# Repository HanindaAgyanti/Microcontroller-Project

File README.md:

<h1 align="left">
  Audio Sistem Pengingat Penyiraman Tanaman
<br></br>

</h1>

## Daftar Isi
* <a href="#deskripsi">Deskripsi</a>
* <a href="#komponen">Komponen</a>
* <a href="#electric">Electric</a>
  - <a href="#blok-diagram">Blok Diagram</a>
  - <a href="#simulasi-tinkercad">Simulasi Tinkercad</a>
  - <a href="#schematic">Schematic</a>
  - <a href="#pcb">PCB</a>
  - <a href="#audio">Audio</a>
* <a href="#3d-design">3D Design</a>
  - <a href="#preview-img">Preview Img</a>
  - <a href="#preview-video">Preview Video</a>
* <a href="#program">Program</a>
  - <a href="#flowchart">Flowchart</a>
  - <a href="arduino-program">Arduino Program</a>
* <a href="#progress">Progress</a>
* <a href="#iklan-produk">Iklan Produk</a>
* <a href="#contact-person">Contact Person</a>
<br></br>

## Deskripsi
<div align="justify">
Sebuah projek mata kuliah Workshop Mikrokontroler membuat Sistem Pendeteksi Penyiram Tanaman diharap mampu membantu masyarakat diberbagai kalangan usia untuk dapat menentukan waktu yang tepat dalam menyiram tanaman menggunakan sensor kelembapan. Dengan adanya project ini juga dapat mencapai sektor lingkungan khususnya pada taman, agar tanaman dapat lebih segar dan tidak layu. Project ini juga sangat bermanfaat untuk sektor pertanian, perkebunan, serta perladangan.<br></br>
  
`#Audio Sistem Pengingat Penyiraman Tanaman` `#Workshop Mikrokontroler` `#Teknik Elektronika` `#Politeknik Elektronika Negeri Surabaya`
</div><br></br>

## Anggota Kelompok
### Rayzanta Ilham D (2122500033)<br> Jobdesk: 3D Design<br>
   <br>
### Fahrian M Rafli  (2122500038)<br> Jobdesk: Non-Tech<br>
   <br>
### Sholihatuz Zahro (2122500049)<br> Jobdesk: Program<br>
   <br>
### Azam Zakariya (2122500051)<br> Jobdesk: Electric<br>
   <br>
### Fadilatul Ilmi M (2122500055)<br> Jobdesk: Audio<br>
   <br>
### Haninda Agyanti F (2122500060)<br> Jobdesk: Ketua&Program<br>
   
<br></br>

## Komponen
### 1. Arduino Uno

<div align = "justify">
Arduino Uno adalah salah satu papan mikrokontroler paling populer dan mudah digunakan untuk pemula serta pengembang berpengalaman. Arduino Uno dirancang berdasarkan mikrokontroler ATmega328P dari Microchip. Berikut adalah penjelasan lebih rinci tentang Arduino Uno:

Fitur Utama Arduino Uno
Mikrokontroler:

ATmega328P
Tegangan Operasional:

7-12V
Tegangan Input:

6-20V
Pin Digital I/O:

14 (termasuk 6 pin PWM)
Pin Analog Input:

6 (A0 hingga A5)
Arus Maksimum per Pin I/O:

40 mA
Arus untuk Pin 3.3V:

50 mA
Memori:

Flash Memory: 32 KB (0.5 KB digunakan oleh bootloader)
SRAM: 2 KB
EEPROM: 1 KB
Clock Speed:

16 MHz
</div><br></br>

### 2. Soil Moisture Sensor

<div align = "justify">

Sensor kelembaban tanah (soil moisture sensor) adalah alat yang digunakan untuk mengukur kadar air dalam tanah. Sensor ini sangat berguna dalam aplikasi seperti sistem irigasi otomatis, pemantauan kondisi tanaman, dan proyek-proyek agrikultur berbasis IoT (Internet of Things). Berikut adalah penjelasan lebih detail tentang cara kerja sensor kelembaban tanah, cara menghubungkannya ke Arduino Uno, dan contoh kode untuk menggunakannya.

Cara Kerja Sensor Kelembaban Tanah
Sensor kelembaban tanah biasanya terdiri dari dua probe yang dimasukkan ke dalam tanah. Prinsip kerjanya adalah mengukur resistansi atau kapasitansi antara dua probe. Air dalam tanah akan mengurangi resistansi atau meningkatkan kapasitansi, sehingga semakin banyak air yang ada, semakin rendah resistansinya (atau semakin tinggi kapasitansinya). Nilai ini kemudian diubah menjadi sinyal analog yang dapat dibaca oleh mikrokontroler seperti Arduino.
</div><br></br>

### 3. Amplifier PAM8403 

<div align = "justify">
PAM8403 adalah amplifier audio kelas D yang sangat efisien dan sering digunakan dalam proyek DIY karena ukurannya yang kecil dan kemampuannya untuk menghasilkan output suara yang cukup keras dengan konsumsi daya yang rendah. PAM8403 dapat memberikan daya 3W per kanal pada beban 4 ohm dengan distorsi yang rendah, menjadikannya pilihan yang populer untuk speaker portabel dan perangkat audio lainnya.
</div><br></br>

### 4. Speaker 0.5W
<br></br>

## Electric
### Blok Diagram
<br></br>
Prinsip kerja dari audio system pengingat penyiram tanaman ini diulai dengan system pertama kali memakai sumber daya yang bersal dari baterai. Ketika sensor soil moisture mendeteksi apakah tanah lembab ( <400) maka audio tidak akan menyala (off) dan jika tanah mencapai nilai (>600) maka audio akan menyala (on). Untuk informasi audio ketika menyala memberi peringatan ketika tanah kering "Siram..Siram..Siram". Jika tanaman yang sudah di siram atau tidak kering makan audio sistem tidak akan menyalakan alarm ataupun pengingat.Amplifier digunakan untuk mengatur volume suara yang akan dikeluarkan audio.

### Simulasi Tinkercad

Link Simulasi: <a href="https://www.tinkercad.com/things/e18MOugMR9O-cool-uusam-sango/editel?tenant=circuits">Tinkercad</a><br>
Link Video: <a href="https://youtu.be/MZAg9T-eXJ4">Youtube</a>

Program Simulasi Tinkercad:

```aruino
int sensorPin = A0;
int buzzerPin = 6;
int ledPin = 4;

void setup() {
  pinMode(sensorPin, INPUT);
  pinMode(buzzerPin, OUTPUT);
  pinMode(ledPin, OUTPUT);
  Serial.begin(9600);
}

void loop() {
  int value = analogRead(sensorPin);
  Serial.println(value); // Menampilkan nilai kelembaban tanah di Serial Monitor
  if (value <= 150) {
    tone(buzzerPin, 200); // Menghasilkan suara pada buzzer
    digitalWrite(ledPin, LOW); // LED mati
    delay(1000); // Menunggu selama 1000 milidetik (1 detik)
  } else {
    noTone(buzzerPin); // Mematikan buzzer
    digitalWrite(ledPin, HIGH); // LED menyala
    delay(1000); // Menunggu selama 1000 milidetik (1 detik)
  }
}
```
<br></br>

### Schematic
<br></br>

### PCB
#### Silkscreen
<br></br>

#### Bottom Layer

#### Preview Video

https://github.com/HanindaAgyanti/Microcontroller-Project/assets/168505485/02a7e13c-888d-486f-8989-f1c24bdb3bce

Link Tutorial Pembuatan Schematic: <a href="https://www.youtube.com/watch?v=J_sLL8TUjsM">Tutorial PCB</a><br></br>

### Audio

Cara mengkonversi audio menjadi bahasa C
1. Membuka audacity
2. Record suara
3. Export -  other uncompressed files - 8000Hz - Raw (header-less) - Unsigned 8-bit PCM
3. Import - Raw Data - File audacity
4. Buka HxD
5. File - Open - File Raw
6. Export - C
7. Masukkan program C ke program

#### Preview Video

https://github.com/HanindaAgyanti/Microcontroller-Project/assets/168505485/dc388206-23a1-4702-8ed6-65cfa78eb401

Link Tutorial Youtube: <a href="https://www.youtube.com/watch?v=oBMv-TfjefU&ab_channel=055_FadilatulIlmiM">Tutorial Konversi Audio</a><br></br>

## 3D Design
### Preview Img
#### Top View

#### Bottom View

#### Dimension

<br></br>

### Preview Video
https://github.com/HanindaAgyanti/Microcontroller-Project/assets/50543100/187bb474-06c7-4d15-9010-6af74fe66d80

Link Tutorial: <a href="https://youtu.be/PaVSHKxSr_M">Youtube</a><br></br>

### Hasil Cetak
<br></br>

## Program
### Flowchart

Cara Kerja:
1. Start (Mulai)
2. Sistem diaktifkan dan memulai proses
3. Inisialisasi Komponen. Pada tahap ini, semua komponen yang diperlukan seperti sensor kelembapan tanah, speaker, dan tombol reset diinisialisasi. Ini bisa melibatkan konfigurasi pin input/output dan inisialisasi modul ADC (Analog to Digital Converter) serta komunikasi serial jika diperlukan.
4. Deteksi Kelembapan Tanah. Sistem membaca nilai kelembapan tanah dari sensor. Nilai ini diambil melalui ADC yang mengonversi sinyal analog dari sensor menjadi nilai digital yang bisa dibaca oleh mikrokontroler.
5. IF Tanah Lembab (Jika Tanah Lembab) Nilai yang didapatkan dari sensor dibandingkan dengan ambang batas yang telah ditentukan. Jika nilai menunjukkan bahwa tanah lembab (misalnya nilai sensor lebih rendah dari ambang batas tertentu), maka proses berikutnya adalah menonaktifkan speaker.
6. True (Benar) - Speaker OFF. Jika kondisi tanah lembab terpenuhi (kondisi benar), speaker akan dimatikan. Ini berarti tidak ada alarm atau indikasi suara yang dihasilkan karena tanah cukup lembab.
7. False (Salah) - Speaker ON. Jika kondisi tanah tidak lembab (kondisi salah), speaker akan diaktifkan. Ini berarti sistem akan memberikan alarm atau indikasi suara untuk menandakan bahwa tanah tidak cukup lembab dan mungkin memerlukan penyiraman.
8. Reset Button (Tombol Reset). Pada titik ini, pengguna dapat menekan tombol reset untuk menonaktifkan speaker meskipun kondisi tanah tidak lembab. Ini memungkinkan pengguna untuk secara manual mengatur ulang status alarm suara.
9. Loop Kembali ke Deteksi Kelembapan Tanah. Setelah kondisi diperiksa dan aksi diambil, sistem kembali ke tahap deteksi kelembapan tanah untuk terus memonitor kondisi tanah.
10. Stop (Berhenti)
<br></br>

### Arduino Program
```arduino
#include <avr/io.h>
#include <avr/eeprom.h>
#include <util/delay.h>
#include <avr/pgmspace.h>
#include <avr/interrupt.h>
#include <avr/sleep.h>
#include "suara.h" // Include the header file with the audio data

volatile bool play = false;
volatile uint8_t track = 0;
volatile uint16_t count = 0;

ISR(TIMER0_COMPA_vect) {
  if (play) {
    if (track == 0) {
      OCR1B = pgm_read_byte(&suara[count]); // Play track 0
      count++;
      if (count >= sizeof(suara)) {
        play = false;
        OCR1B = 0;
      }
    }
  }
}

void initPWM(void);
void TimerInit(void);
void initADC(void);

int main(void) {
  DDRD |= _BV(DDD6); // Set PD6 (OC0A/OC1A) as output for PWM
  PORTD |= _BV(PORTD2) | _BV(PORTD3); // Enable pull-up resistors on PD2 and PD3

  initPWM();
  TimerInit();
  initADC(); // Initialize ADC

  sei();

  while (1) {
    // Start ADC conversion
    ADCSRA |= (1 << ADSC); 
    // Wait for conversion to complete
    while (ADCSRA & (1 << ADSC)); 
    uint16_t soilMoisture = ADC; 

    // Logic to control audio playback based on soil moisture levels
    if (soilMoisture >= 600 && !play) { // Adjust the dry threshold as needed
      play = true;
      track = 0;
      count = 0;
    } else if (soilMoisture <= 400) { // Adjust the wet threshold as needed
      play = false;
      OCR1B = 0; // Stop audio playback
    }
  }
}

void initPWM() {
  DDRB |= _BV(DDB2); // Set PB2 (OC1B) as output for PWM
  TCCR1A = _BV(WGM10) | _BV(COM1B1); // Fast PWM, 8-bit
  TCCR1B = _BV(WGM12) | _BV(CS10);   // Fast PWM, no prescaler
  OCR1B = 0; // Initialize PWM output to 0
}

void TimerInit() {
  TCCR0A = _BV(WGM01); // CTC mode
  TCCR0B = _BV(CS01);  // Prescaler 8
  OCR0A = 250;
  TIMSK0 |= _BV(OCIE0A); // Enable compare match interrupt
}

void initADC() {
  ADMUX = _BV(REFS0); // Select AVCC as voltage reference and set ADC0 as default input
  ADCSRA = _BV(ADEN) | _BV(ADPS2) | _BV(ADPS1) | _BV(ADPS0); // Enable ADC and set prescaler to 128
}
```
<br></br>
## Progress
### 1. Hasil PCB
<br></br>

### 2. Perakitan PCB
<br></br>

### 3. Pinout PCB
<br></br>

### 4. 3D
<br></br>

### 5. Input Progam

### 6. Pengambilan Data
<br></br>

## Dokumentasi
<br></br>
<br></br>
<br></br>

https://github.com/HanindaAgyanti/Microcontroller-Project/assets/168505485/8251bc53-0eb5-4819-916f-895ad86c14af

<br></br>
## Video Simulasi
https://github.com/HanindaAgyanti/Microcontroller-Project/assets/168505485/e376ab55-6ebf-4a3b-9dbd-66905923db76

Link Video: <a href="https://youtu.be/01_OHSK8EwU?si=7nykVMJsQNBZ06yZ">Youtube</a><br></br>

## Iklan Produk

<br></br>

https://github.com/HanindaAgyanti/Microcontroller-Project/assets/50543100/cd2beb3d-e490-4797-92b8-2a613e396048

<br></br>

## Contact Person
> Instagram [@ryan.carlsenn](https://www.instagram.com/ryan.carlsenn/)

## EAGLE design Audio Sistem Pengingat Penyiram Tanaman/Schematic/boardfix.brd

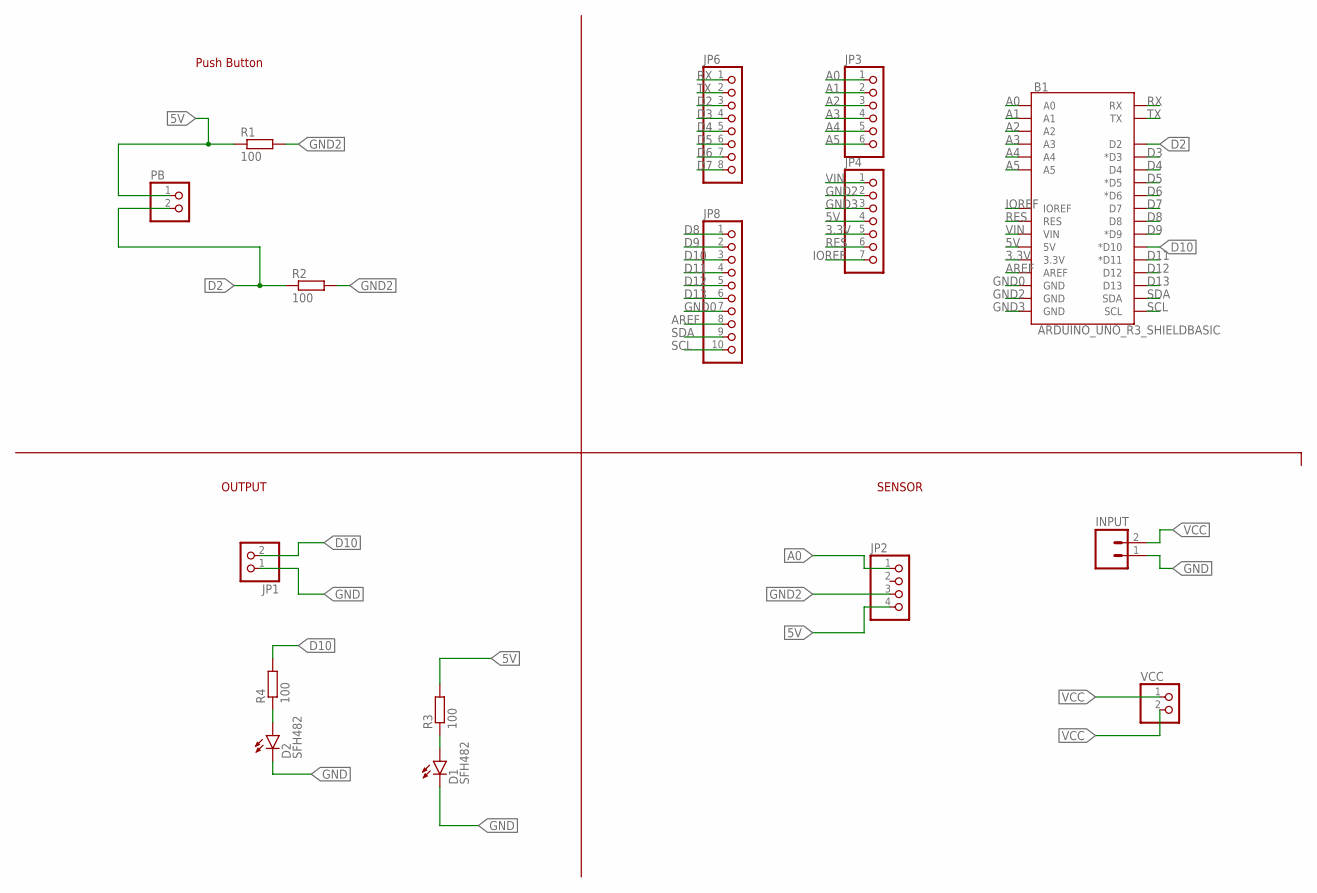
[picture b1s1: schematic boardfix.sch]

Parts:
B1: ARDUINO_UNO_R3_SHIELDBASIC; UNO_R3_SHIELD
D1, D2: SFH482
INPUT: M02; 02P
JP1: PINHD-1X2; 1X02
JP2: PINHD-1X4; 1X04
JP3: PINHD-1X6; 1X06
JP4: PINHD-1X7; 1X07
JP6: PINHD-1X8; 1X08
JP8: PINHD-1X10; 1X10
PB: PINHD-1X2; 1X02
R1, R2, R3, R4: 100; 0207/7
VCC: PINHD-1X2; 1X02

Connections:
3.3V: B1.3.3V, JP4.5
5V: B1.5V, JP2.4, JP4.4, PB.1, R1.1, R3.2
A0: B1.A0, JP2.1, JP3.1
A1: B1.A1, JP3.2
A2: B1.A2, JP3.3
A3: B1.A3, JP3.4
A4: B1.A4, JP3.5
A5: B1.A5, JP3.6
AREF: B1.AREF, JP8.8
D2: B1.D2, JP6.3, PB.2, R2.1
D3: B1.D3 (*D3), JP6.4
D4: B1.D4, JP6.5
D5: B1.D5 (*D5), JP6.6
D6: B1.D6 (*D6), JP6.7
D7: B1.D7, JP6.8
D8: B1.D8, JP8.1
D9: B1.D9 (*D9), JP8.2
D10: B1.D10 (*D10), JP1.2, JP8.3, R4.2
D11: B1.D11 (*D11), JP8.4
D12: B1.D12, JP8.5
D13: B1.D13, JP8.6
GND: D1.K (C), D2.K (C), INPUT.1, JP1.1
GND0: B1.GND@2 (GND), JP8.7
GND2: B1.GND@1 (GND), JP2.3, JP4.2, R1.2, R2.2
GND3: B1.GND@0 (GND), JP4.3
IOREF: B1.IOREF, JP4.7
unnamed: D1.A, R3.1
unnamed: D2.A, R4.1
RES: B1.RES, JP4.6
RX: B1.RX, JP6.1
SCL: B1.SCL, JP8.10
SDA: B1.SDA, JP8.9
TX: B1.TX, JP6.2
VCC: INPUT.2, VCC.1, VCC.2
VIN: B1.VIN, JP4.1

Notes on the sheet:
Push Button
OUTPUT
SENSOR

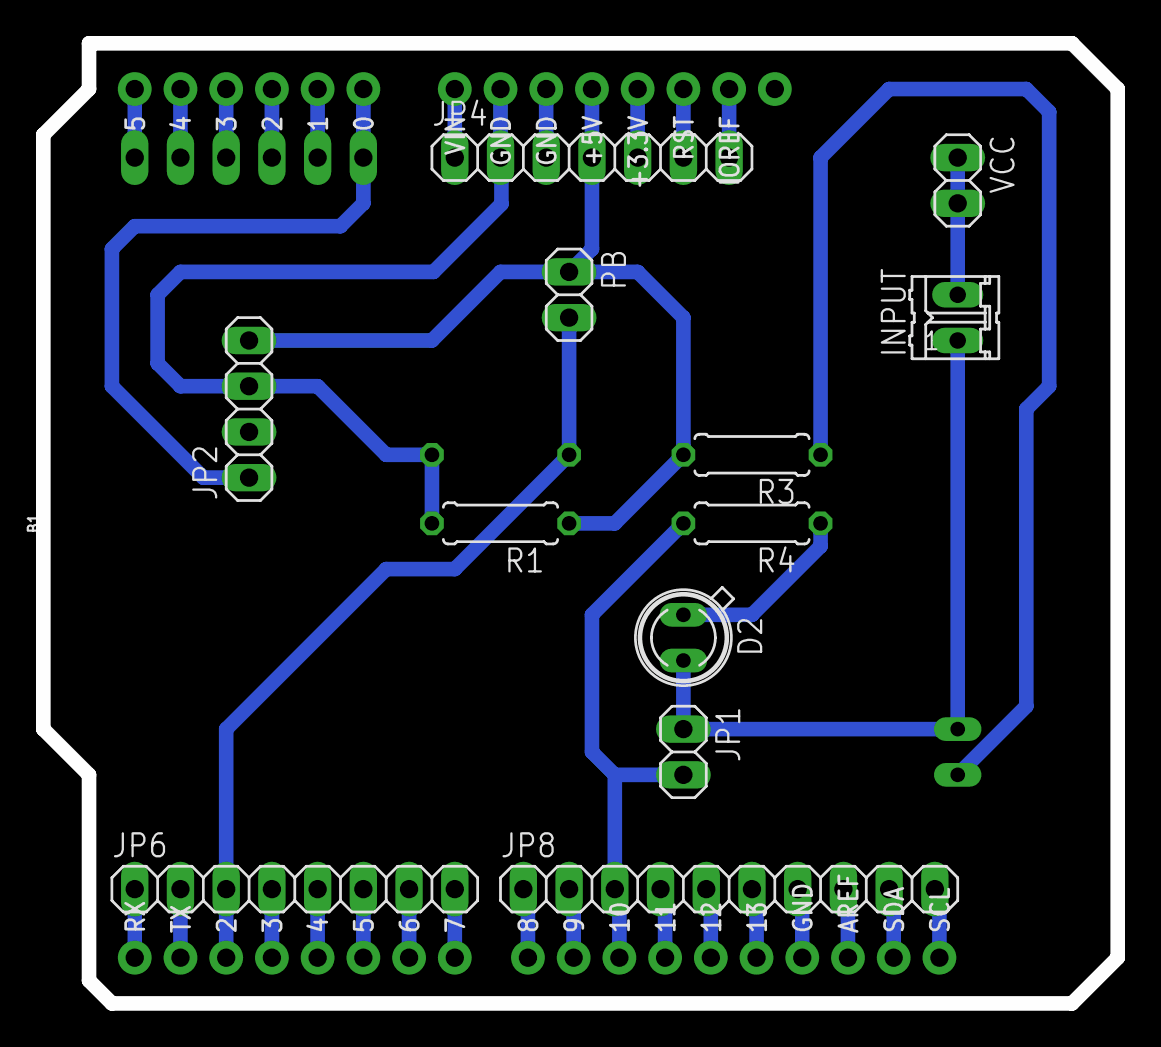
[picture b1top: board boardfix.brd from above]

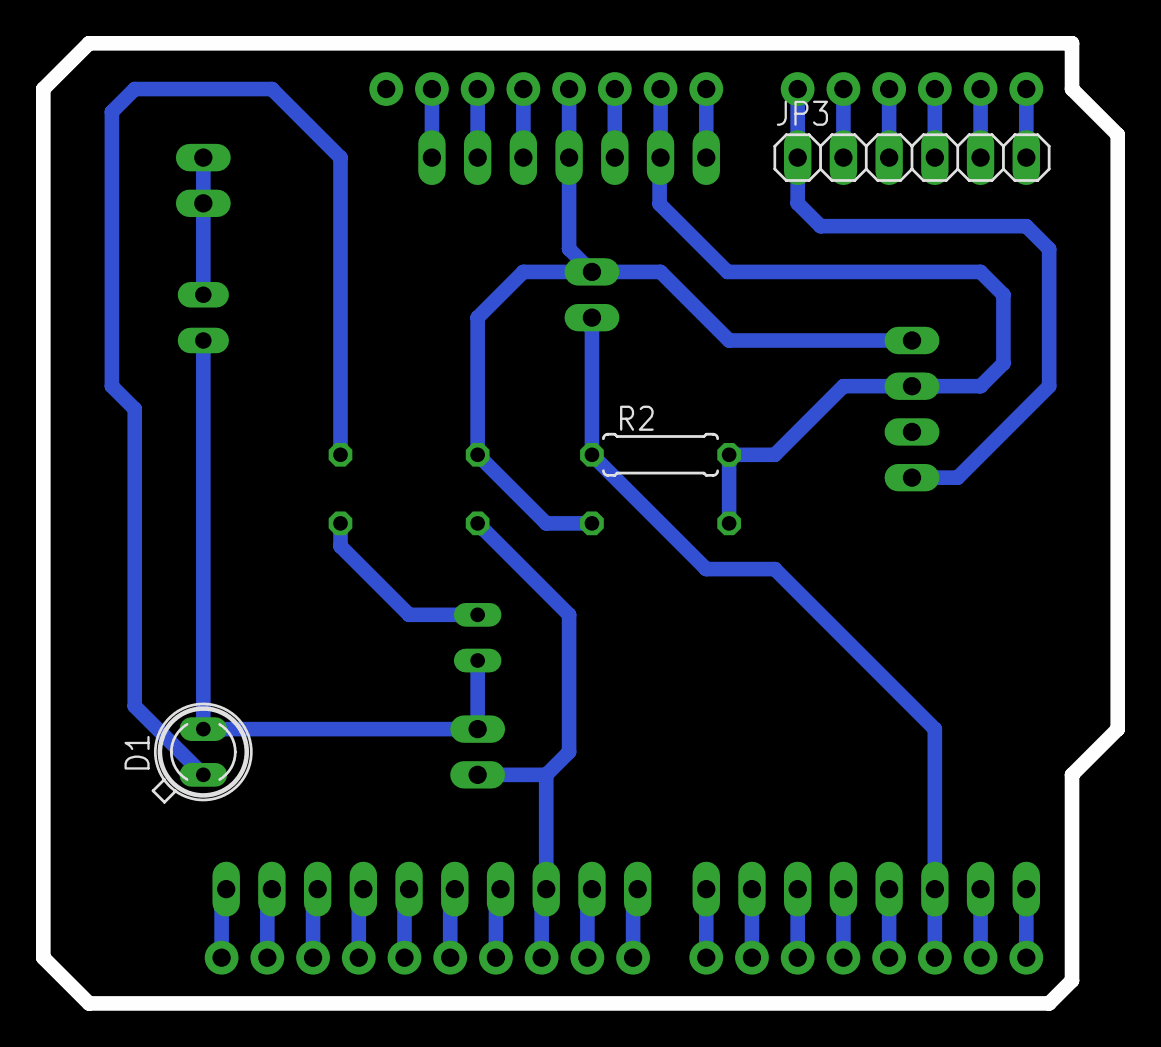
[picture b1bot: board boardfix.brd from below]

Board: 2 copper layers, 59.7 x 53.3 mm, 16 parts (3 on the bottom side), 35 nets.

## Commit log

2024-05-11 Readme
2024-05-19 Rename image.png to Schematic.png
2024-05-19 Rename Screenshot 2024-05-19 091646.png to Silkscreen.png
2024-05-19 Rename Screenshot 2024-05-19 091720.png to Bottom Layer.png
2024-05-21 Rename Screenshot 2024-05-14 084041.png to Progress1.png
2024-05-21 Rename Screenshot 2024-05-14 084048.png to progres 1-1.png
2024-05-21 Rename WhatsApp Image 2024-05-20 at 19.27.22 (1).jpeg to progres 2.jpeg
2024-05-21 Rename progres 2.jpeg to progres 2-1.jpeg
2024-05-21 Rename WhatsApp Image 2024-05-20 at 19.27.22.jpeg to progres 2-2.jpeg
2024-05-21 Rename WhatsApp Image 2024-05-20 at 19.27.23.jpeg to progres 2-3.jpeg
2024-05-23 Rename HxD.jpg to Progres 1.jpg
2024-05-23 Rename WhatsApp Image 2024-05-23 at 13.23.07_8d1c4dd9.jpg to Progress 2.jpg
2024-05-23 Rename WhatsApp Image 2024-05-23 at 13.23.08_078f7b4a.jpg to Progess 3.jpg
2024-05-23 Create Design sistem
2024-05-27 Rename WhatsApp Image 2024-05-23 at 13.13.02.jpeg to Buttom.jpeg
2024-05-27 Rename Buttom.jpeg to Top.jpeg
2024-05-27 Rename WhatsApp Image 2024-05-23 at 12.40.16_a2ab56ff.jpg to Perakitan PCB.jpg
2024-05-27 Rename WhatsApp Image 2024-05-23 at 13.13.07_b5fb8bd8.jpg to Hasil PCB Jadi.jpg
2024-05-27 Rename WhatsApp Image 2024-05-23 at 14.44.37_03a4dccb.jpg to Perakitan PCB.jpg
2024-05-27 Rename WhatsApp Image 2024-05-24 at 17.57.00_7167c98f.jpg to Bagian-bagian pada Shield PCB.jpg
2024-05-27 Rename WhatsApp Image 2024-05-26 at 11.24.18_902c5cd1.jpg to Hasil 3D.jpg
2024-05-27 Rename WhatsApp Image 2024-05-27 at 15.35.08_b7d468f7.jpg to Input Program.jpg
2024-05-27 Rename WhatsApp Image 2024-05-23 at 13.13.02 (1).jpeg to Buttom.jpeg
2024-05-27 Rename Buttom.jpeg to PCB Jadi.jpeg
2024-05-27 Rename WhatsApp Image 2024-05-27 at 16.08.31_9b11449b.jpg to Program2.jpg
2024-05-28 Rename WhatsApp Image 2024-05-28 at 09.11.35.jpeg to Azam.jpeg
2024-05-28 Rename WhatsApp Image 2024-05-28 at 09.15.54.jpeg to Rayzan.jpeg
2024-05-28 Rename WhatsApp Image 2024-05-28 at 09.17.03.jpeg to Ilmi.jpeg
2024-05-28 Rename WhatsApp Image 2024-05-28 at 09.37.47.jpeg to Rian.jpeg
2024-05-28 Rename WhatsApp Image 2024-05-28 at 10.16.46.jpeg to Iza.jpeg
2024-05-28 Rename WhatsApp Image 2024-05-28 at 10.16.48.jpeg to Hanin.jpeg
2024-05-28 Rename WhatsApp Image 2024-05-28 at 10.37.00.jpeg to Pengambilan data.jpeg
2024-06-02 Create 3D Design
2024-06-03 Rename WhatsApp Image 2024-05-26 at 11.24.15.jpeg to Hasil Cetak.jpeg
2024-06-03 Rename WhatsApp Image 2024-06-03 at 17.38.42_86c28c49.jpg to Rayza2.jpg
2024-06-04 Create Video Simulasi
2024-06-09 Rename Blue and White Futuristic Games Competitions Flyer (3)_page-0001.jpg to Flyer.jpg

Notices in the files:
parts and their libraries:
SparkFun-Boards: Licensing: Creative Commons ShareAlike 4.0 International - https://creativecommons.org/licenses/by-sa/4.0
